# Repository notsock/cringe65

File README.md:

# cringe65
65% keyboard with 3 split spacebar support and MX, Alps, and Kailh socket compatability.

# Features
- USBLC6-2SC6 for ESD protection
- USB Type C
- GH60 Mounting
- Kailh Socket, MX switch, and Alps compatibility  
- Through hole diodes for easier assembly
- 6.25u or 2u x 1.25u x 3u support

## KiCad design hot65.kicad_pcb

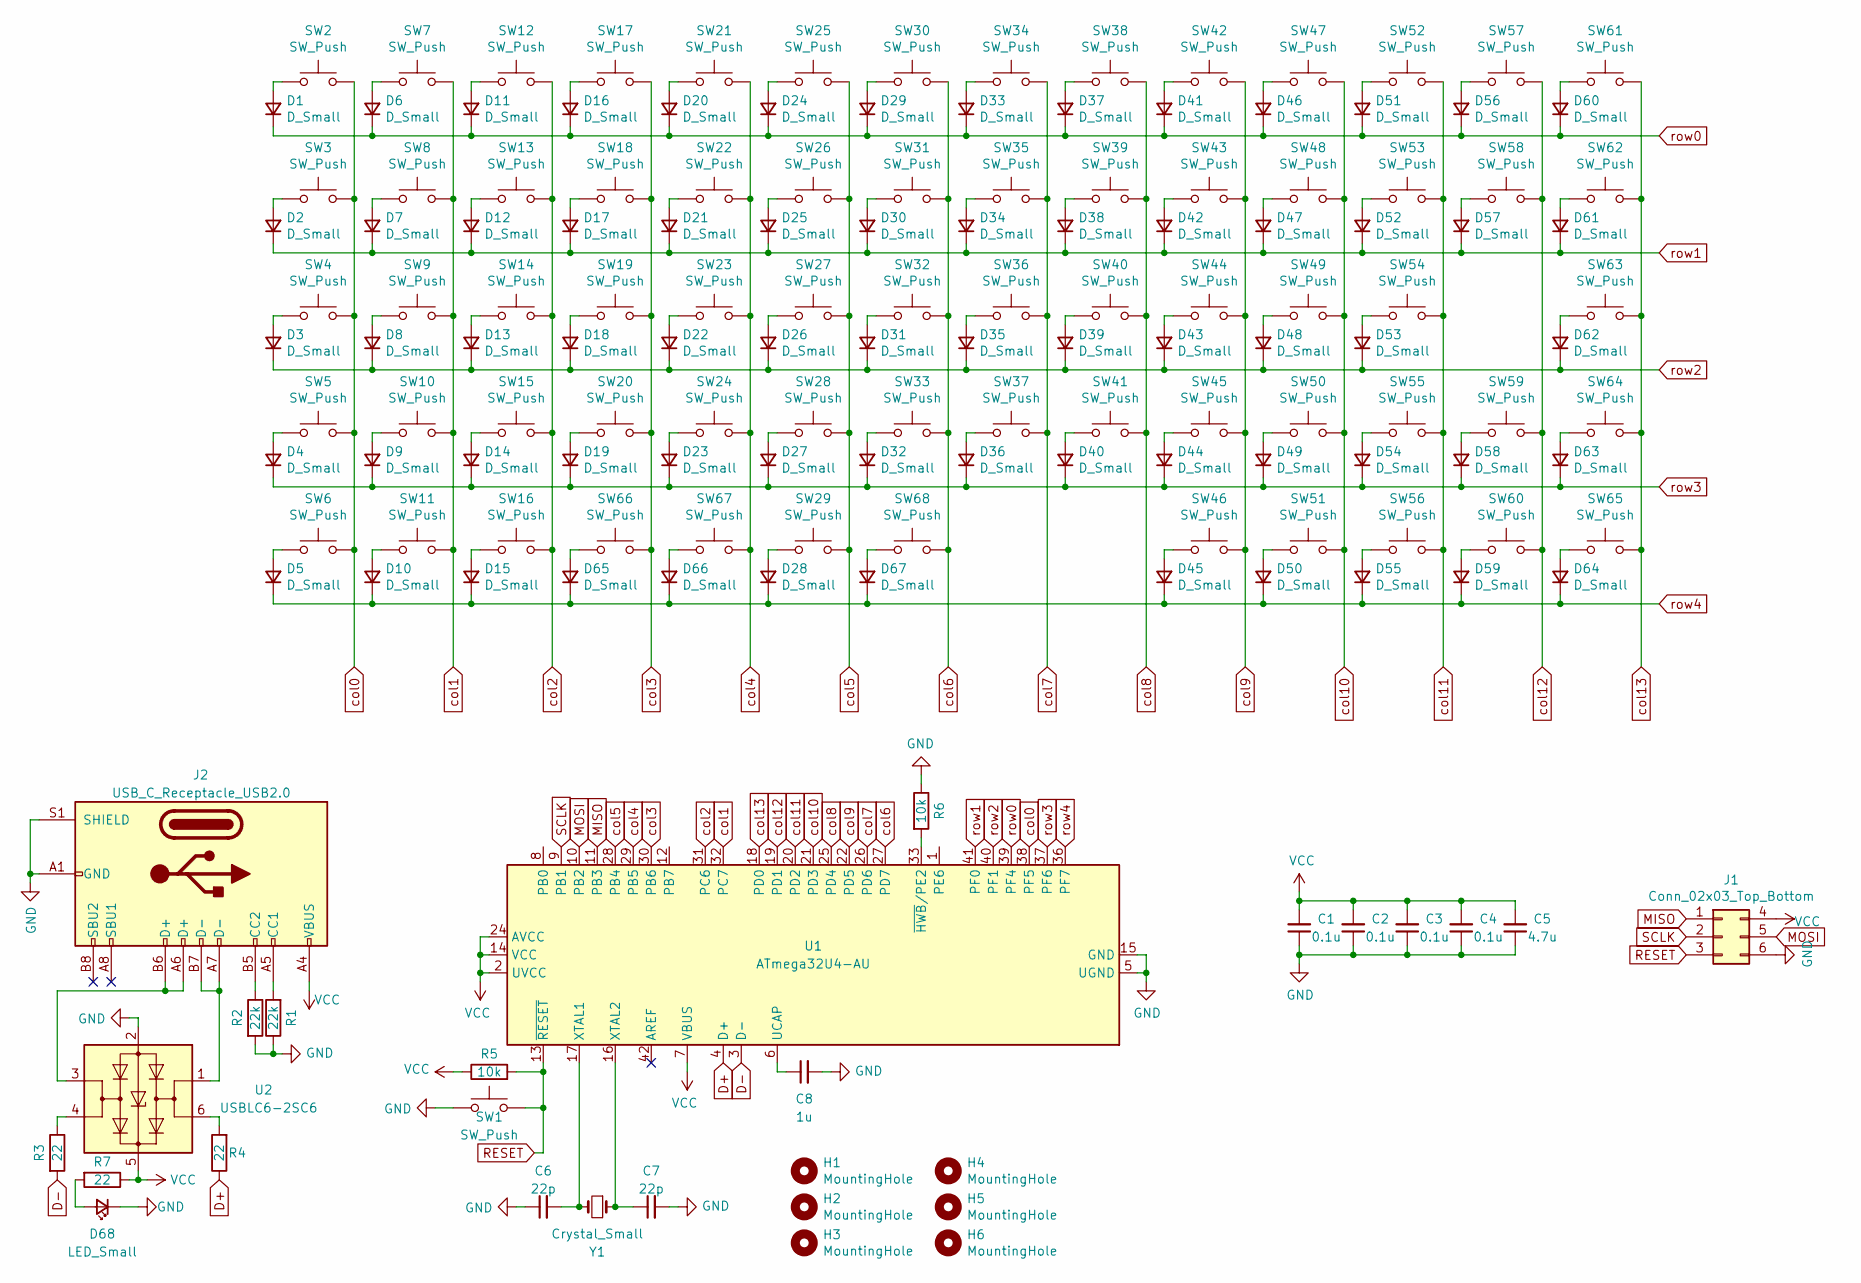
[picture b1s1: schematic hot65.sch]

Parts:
C1, C2, C3, C4: 0.1u; C_0603_1608Metric_Pad1.08x0.95mm_HandSolder
C5: 4.7u; C_0603_1608Metric_Pad1.08x0.95mm_HandSolder
C6, C7: 22p; C_0603_1608Metric_Pad1.08x0.95mm_HandSolder
C8: 1u; C_0603_1608Metric_Pad1.08x0.95mm_HandSolder
D1, D2, D3, D4, D5, D6, D7, D8, D9, D10, D11, D12, D13, D14, D15, D16, D17, D18, D19, D20, D21, D22, D23, D24, D25, D26, D27, D28, D29, D30, D31, D32, D33, D34, D35, D36, D37, D38, D39, D40, D41, D42, D43, D44, D45, D46, D47, D48, D49, D50, D51, D52, D53, D54, D55, D56, D57, D58, D59, D60, D61, D62, D63, D64, D65, D66, D67: D_Small; D_T-1_P5.08mm_Horizontal
D68: LED_Small; LED_0603_1608Metric
H1, H2, H3, H4: MountingHole; M2_slot
H5, H6: MountingHole; M2_long_slot
J1: Conn_02x03_Top_Bottom; PinHeader_2x03_P1.00mm_Vertical
J2: USB_C_Receptacle_USB2.0; USB_C_Receptacle_XKB_U262-16XN-4BVC11
R1, R2: 22k; R_0603_1608Metric_Pad0.98x0.95mm_HandSolder
R3, R4, R7: 22; R_0603_1608Metric_Pad0.98x0.95mm_HandSolder
R5, R6: 10k; R_0603_1608Metric_Pad0.98x0.95mm_HandSolder
SW1: SW_Push; SW_Push_1P1T_NO_CK_KSC6xxJ
SW2, SW7, SW8, SW9, SW10, SW12, SW13, SW14, SW15, SW17, SW18, SW19, SW20, SW21, SW22, SW23, SW24, SW25, SW26, SW27, SW28, SW30, SW31, SW32, SW33, SW34, SW35, SW36, SW37, SW38, SW39, SW40, SW41, SW42, SW43, SW44, SW45, SW46, SW47, SW48, SW49, SW50, SW51, SW52, SW53, SW54, SW55, SW56, SW57, SW58, SW59, SW60, SW64, SW65: SW_Push; MXSocketAlps
SW3, SW62: SW_Push; MXSocketAlps_1.5u
SW4: SW_Push; MXSocketAlps_1.75u
SW5, SW61, SW66: SW_Push; MXSocketAlps_2u
SW6, SW11, SW16, SW67: SW_Push; MXSocketAlps_1.25u
SW29: SW_Push; MXSocketAlps_6.25u
SW63: SW_Push; MXSocketAlps_2.25u
SW68: SW_Push; MXSocketAlps_3u
U1: ATmega32U4-AU; TQFP-44_10x10mm_P0.8mm
U2: USBLC6-2SC6; SOT-23-6
Y1: Crystal_Small; Crystal_SMD_5032-2Pin_5.0x3.2mm_HandSoldering

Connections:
D+: R4.1, U1.4 (D+)
D-: R3.2, U1.3 (D-)
GND: C1.1, C2.1, C3.1, C4.1, C5.1, C6.1, C7.2, C8.2, D68.1 (K), J1.6, J2.A1 (GND), J2.A12 (GND), J2.B1 (GND), J2.B12 (GND), J2.S1 (SHIELD), R1.1, R2.2, R6.1, SW1.1, U1.5 (UGND), U1.15 (GND), U1.23 (GND), U1.35 (GND), U1.43 (GND), U2.2 (GND)
MISO: J1.1, U1.11 (PB3)
MOSI: J1.5, U1.10 (PB2)
unnamed: C6.2, U1.17 (XTAL1), Y1.2
unnamed: C7.1, U1.16 (XTAL2), Y1.1
unnamed: C8.1, U1.6 (UCAP)
unnamed: D1.2 (A), SW2.1
unnamed: D2.2 (A), SW3.1
unnamed: D3.2 (A), SW4.1
unnamed: D4.2 (A), SW5.1
unnamed: D5.2 (A), SW6.1
unnamed: D6.2 (A), SW7.1
unnamed: D7.2 (A), SW8.1
unnamed: D8.2 (A), SW9.1
unnamed: D9.2 (A), SW10.1
unnamed: D10.2 (A), SW11.1
unnamed: D11.2 (A), SW12.1
unnamed: D12.2 (A), SW13.1
unnamed: D13.2 (A), SW14.1
unnamed: D14.2 (A), SW15.1
unnamed: D15.2 (A), SW16.1
unnamed: D16.2 (A), SW17.1
unnamed: D17.2 (A), SW18.1
unnamed: D18.2 (A), SW19.1
unnamed: D19.2 (A), SW20.1
unnamed: D20.2 (A), SW21.1
unnamed: D21.2 (A), SW22.1
unnamed: D22.2 (A), SW23.1
unnamed: D23.2 (A), SW24.1
unnamed: D24.2 (A), SW25.1
unnamed: D25.2 (A), SW26.1
unnamed: D26.2 (A), SW27.1
unnamed: D27.2 (A), SW28.1
unnamed: D28.2 (A), SW29.1
unnamed: D29.2 (A), SW30.1
unnamed: D30.2 (A), SW31.1
unnamed: D31.2 (A), SW32.1
unnamed: D32.2 (A), SW33.1
unnamed: D33.2 (A), SW34.1
unnamed: D34.2 (A), SW35.1
unnamed: D35.2 (A), SW36.1
unnamed: D36.2 (A), SW37.1
unnamed: D37.2 (A), SW38.1
unnamed: D38.2 (A), SW39.1
unnamed: D39.2 (A), SW40.1
unnamed: D40.2 (A), SW41.1
unnamed: D41.2 (A), SW42.1
unnamed: D42.2 (A), SW43.1
unnamed: D43.2 (A), SW44.1
unnamed: D44.2 (A), SW45.1
unnamed: D45.2 (A), SW46.1
unnamed: D46.2 (A), SW47.1
unnamed: D47.2 (A), SW48.1
unnamed: D48.2 (A), SW49.1
unnamed: D49.2 (A), SW50.1
unnamed: D50.2 (A), SW51.1
unnamed: D51.2 (A), SW52.1
unnamed: D52.2 (A), SW53.1
unnamed: D53.2 (A), SW54.1
unnamed: D54.2 (A), SW55.1
unnamed: D55.2 (A), SW56.1
unnamed: D56.2 (A), SW57.1
unnamed: D57.2 (A), SW58.1
unnamed: D58.2 (A), SW59.1
unnamed: D59.2 (A), SW60.1
unnamed: D60.2 (A), SW61.1
unnamed: D61.2 (A), SW62.1
unnamed: D62.2 (A), SW63.1
unnamed: D63.2 (A), SW64.1
unnamed: D64.2 (A), SW65.1
unnamed: D65.2 (A), SW66.1
unnamed: D66.2 (A), SW67.1
unnamed: D67.2 (A), SW68.1
unnamed: D68.2 (A), R7.2
unnamed: J2.A5 (CC1), R1.2
unnamed: J2.A6 (D+), J2.B6 (D+), U2.3 (I/O2)
unnamed: J2.A7 (D-), J2.B7 (D-), U2.1 (I/O1)
unnamed: J2.B5 (CC2), R2.1
unnamed: R3.1, U2.4 (I/O2)
unnamed: R4.2, U2.6 (I/O1)
unnamed: R6.2, U1.33 (~HWB~/PE2)
RESET: J1.3, R5.2, SW1.2, U1.13 (~RESET)
SCLK: J1.2, U1.9 (PB1)
VCC: C1.2, C2.2, C3.2, C4.2, C5.2, J1.4, J2.A4 (VBUS), J2.A9 (VBUS), J2.B4 (VBUS), J2.B9 (VBUS), R5.1, R7.1, U1.2 (UVCC), U1.7 (VBUS), U1.14 (VCC), U1.24 (AVCC), U1.34 (VCC), U1.44 (AVCC), U2.5 (VBUS)
col0: SW2.2, SW3.2, SW4.2, SW5.2, SW6.2, U1.38 (PF5)
col1: SW7.2, SW8.2, SW9.2, SW10.2, SW11.2, U1.32 (PC7)
col2: SW12.2, SW13.2, SW14.2, SW15.2, SW16.2, U1.31 (PC6)
col3: SW17.2, SW18.2, SW19.2, SW20.2, SW66.2, U1.30 (PB6)
col4: SW21.2, SW22.2, SW23.2, SW24.2, SW67.2, U1.29 (PB5)
col5: SW25.2, SW26.2, SW27.2, SW28.2, SW29.2, U1.28 (PB4)
col6: SW30.2, SW31.2, SW32.2, SW33.2, SW68.2, U1.27 (PD7)
col7: SW34.2, SW35.2, SW36.2, SW37.2, U1.26 (PD6)
col8: SW38.2, SW39.2, SW40.2, SW41.2, U1.25 (PD4)
col9: SW42.2, SW43.2, SW44.2, SW45.2, SW46.2, U1.22 (PD5)
col10: SW47.2, SW48.2, SW49.2, SW50.2, SW51.2, U1.21 (PD3)
col11: SW52.2, SW53.2, SW54.2, SW55.2, SW56.2, U1.20 (PD2)
col12: SW57.2, SW58.2, SW59.2, SW60.2, U1.19 (PD1)
col13: SW61.2, SW62.2, SW63.2, SW64.2, SW65.2, U1.18 (PD0)
row0: D1.1 (K), D6.1 (K), D11.1 (K), D16.1 (K), D20.1 (K), D24.1 (K), D29.1 (K), D33.1 (K), D37.1 (K), D41.1 (K), D46.1 (K), D51.1 (K), D56.1 (K), D60.1 (K), U1.39 (PF4)
row1: D2.1 (K), D7.1 (K), D12.1 (K), D17.1 (K), D21.1 (K), D25.1 (K), D30.1 (K), D34.1 (K), D38.1 (K), D42.1 (K), D47.1 (K), D52.1 (K), D57.1 (K), D61.1 (K), U1.41 (PF0)
row2: D3.1 (K), D8.1 (K), D13.1 (K), D18.1 (K), D22.1 (K), D26.1 (K), D31.1 (K), D35.1 (K), D39.1 (K), D43.1 (K), D48.1 (K), D53.1 (K), D62.1 (K), U1.40 (PF1)
row3: D4.1 (K), D9.1 (K), D14.1 (K), D19.1 (K), D23.1 (K), D27.1 (K), D32.1 (K), D36.1 (K), D40.1 (K), D44.1 (K), D49.1 (K), D54.1 (K), D58.1 (K), D63.1 (K), U1.37 (PF6)
row4: D5.1 (K), D10.1 (K), D15.1 (K), D28.1 (K), D45.1 (K), D50.1 (K), D55.1 (K), D59.1 (K), D64.1 (K), D65.1 (K), D66.1 (K), D67.1 (K), U1.36 (PF7)

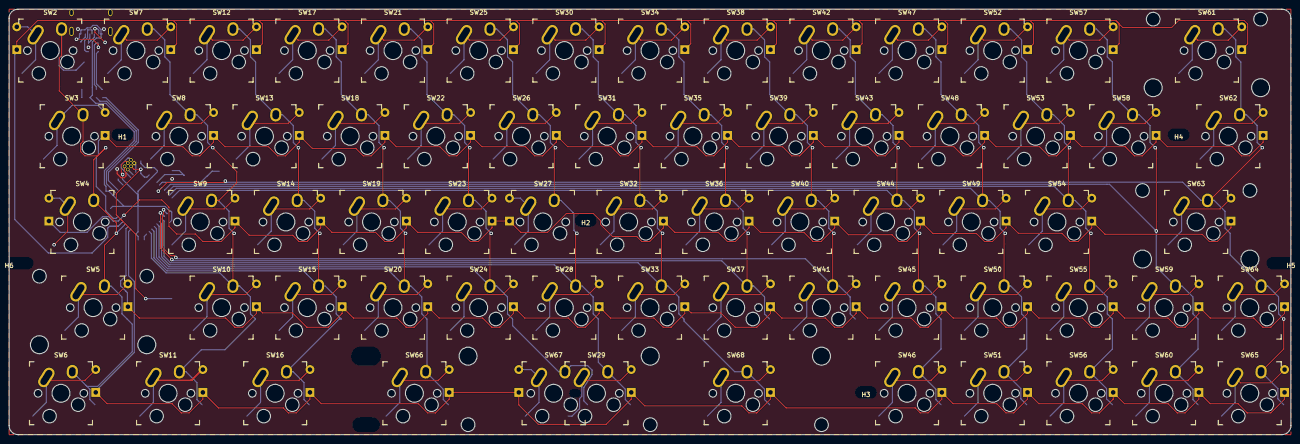
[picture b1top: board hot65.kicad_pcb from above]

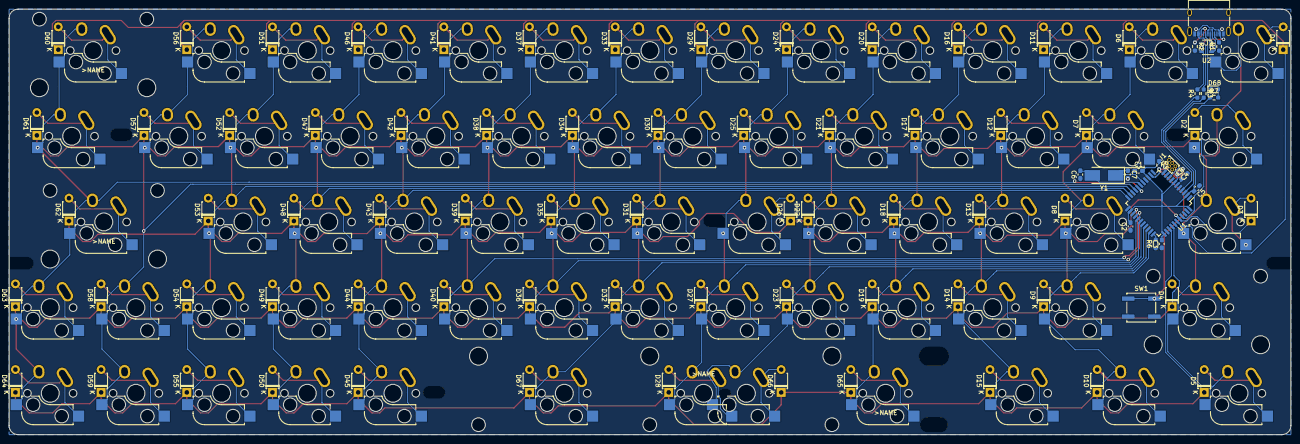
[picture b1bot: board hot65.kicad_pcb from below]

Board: 2 copper layers, 285.0 x 94.6 mm, 162 parts (89 on the bottom side), 105 nets.

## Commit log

2021-04-21 rev 1
2021-04-21 v.0.7
2021-04-26 v.1.0
2021-04-26 new readme
2021-04-26 readme updated
2021-04-27 v.1.1 Fixed drill errors
2021-05-17 v1.1
    Fixed minor issues
2021-05-17 Update README.md
    Spelling
